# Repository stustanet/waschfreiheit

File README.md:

# Waschen in Freiheit !!!
## Was ist das?
Dieses Projekt soll verhindern, dass die armen Studenten unnötig lange mit der Suche nach einer freien Waschmaschine verbringen. Dazu soll der Status aller Maschinen erfasst werden um diese dann online abfragbar zu machen. Will man dann Waschen kann man direkt zu einer freien Maschine laufen und muss nicht erst in jedem Waschraum vorbeischauen, nur um festzustellen, dass dieser schon belegt ist.

## Aufbau
Der aktuelle Plan sieh in etwa so aus:

```
                                     +---+
+---Raum------------------------+    |   |
|                               |    | F |
|  WM <- Sensor  \              |    | U |
|                 => Knoten <~~~|~~~>| N |
|  WM <- Sensor  /              |    | K |
|                               |    |   |
+-------------------------------+    |   |
                                     |   |     +--------+    +-----------+
                                     |   |<~~~>| Bridge |--->| Webserver |
+---Raum------------------------+    |   |     +--------+    +-----------+
|                               |    |   |
|  WM <- Sensor  \              |    |   |
|                 => Knoten <~~~|~~~>|   |
|  WM <- Sensor  /              |    |   |
|                               |    |   |
+-------------------------------+    |   |
                                     |   |
                                     |   |
+---Raum------------------------+    |   |
|                               |    |   |
|  WM <- Sensor ===> Knoten <~~~|~~~>|   |
|                               |    |   |
+-------------------------------+    |   |
                                     +---+
    
```

### Sensoren
Ein Sensor misst den Stromverbrauch einer Maschine. Dies geschieht über einen Hallsensor am Stromkabel.

### Knoten
Ein Knoten besteht aus einem Mikroprozessor (STM32F103C8T6 (V1) oder STM32F401RBT6(V2), Kleiner 32bit ARM) und einem 433Mhz Funkchip (Sx1276, LoRa Modulation).
An einen Knoten sind ein oder mehrere Sensoren angeschlossen. Die Sensordaten werden dann ausgewertet und bei einer Statusänderung wird ein Signal über die Funkschnittstelle gesendet.
Außerdem ist es die Aufgabe eines Knotens Nachrichten anderer Knoten weiterzuleiten, diese bilden quasi ein Mesh Netzwerk.

### Bridge
Es gibt im ganzen System genau eine Bridge (Gateway, Master Node), diese besteht aus einem Funkteil und einem Raspi. Die Aufgabe der Bridge ist es die Statusänderungen vom Mesh Netzwerk zu empfangen und diese dann per IP an einen Webserver weiterzuleiten, der diese dann anzeigt. Zusätzlich verwaltet die Bridge das Netzwerk und die Sensorparameter.

### Webserver
Der Webserver bekommt die Daten von der Bridge und zeigt den aktuellen Status an.

## Statuserkennung
Die Statuserkennung basiert auf Messwerten, die ein am Stromkabel befestigter Hall-Sensor liefert.
Um aus diesen Werten schlussendlich zu erkennen ob eine Maschine in Benutzung ist, durchläuft das Signal eine Reihe von Filtern.

### Analoger Teil
#### Wechselspannungs-Verstärker
Zuerst wird das Signal vom Hall-Sensor verstärkt. Der Verstärker hat für DC einen Verstärkungsfaktor von 1, es werden also nur Änderungen verstärkt.
#### Tiefpass
Bevor das Signal vom ADC digitalisiert wird, wird es mit einem RC-Filter geglättet. Dieser Tiefpass darf nicht zu träge sein, eine höhere Trägheit die Amplitude verringert.

### Digitaler Filter, Stufe 1 (Input)
Die erste Stufe bekommt die Messwerte des ADCs, sie wird für jede Messung einmal aufgerufen.
#### Absolutwertbestimmung
Da das Signal eine Wechselspannung mit dem Mittelpunkt von ca. der halben Betriebsspannung ist, muss zuerst der Absolutwert (Abweichung vom Mittelwert) bestimmt werden.
Dazu wird ein Mittelwert bestimmt, der für jeden Messwert, der drüber liegt um einen kleinen Wert erhöht wird (bzw. verringert wird, wenn der Messwert niedrieger ist).
Die Differenz zwischen dem Mittelwert und dem aktuellen Messwert ist der Absolutwert.
#### Digitaler Tiefpass
Der Absolutwert wird über einen Digitalen Tiefpass geglättet. Hier ist eine wesentlich stärkere Glättung möglich als vor dem Absolutwertfilter, da keine Amplitude verloren geht.

### Digitaler Filter, Stufe 2 (Frames)
In bestimmten Abständen (Frames) wird der aktuelle Tiefpasswert der Stufe 1 an die Stufe 2 weitergegeben. Der Abstand ist die "Framesize"
Die Stufe 2 wird einmal pro Frame aktualisiert. Die letzten "Window Size" Frame-Werte werden gespeichert, aus diesen wird der aktuelle Wert des Filters berechnet.
#### Blockfilter (Consec reject filter)
Alle Werte die nicht größer als ein Grenzwert ("Reject Threshold") sind und nicht mind. "Reject Consec" Werte davor auch über dem Grenzwert liegen werden bei der Berechnung des aktuellen Wertes ignoriert.

Beispiel:
Angenommen der Threshold wäre 5 und der "Consec count" wäre 3, dann würden nur die markierten Werte verwendet werden.

    3 9 8 2 7 8 9 6 3 4 9 2 1 6 7 8 9 9 9 3 4 7 8 2
            ^ ^ ^ ^           ^ ^ ^ ^ ^ ^

#### Durchschnittswert
Der aktuelle Filterwert ist der Durchschnitt aller Werte im aktuellen Fenster. Werte die vom Blockfilter ignoriert werden gehen mit 0 in den Durchschnitt ein.
#### Interner Status
Abhängig vom aktuellen Filterwert und dem aktuellen internen Status wird anhand von festgelegten Grenzwerten bestimmt, ob ein Zustandsübergang stattfindet.
Bei einem Zustandsübergang wird ggf. die "Window Size" angepasst. Für jeden internen Zustand ist festgelegt, ob die Maschine in diesem Zustand belegt oder frei ist.
Nur Änderungen des Belegtzustandes werden über das Netzwerk gesendet.

## Ich will das complien!
* Ggf. ARM Toolchain installieren.
* Dieses Repo klonen.
* git submodule init
* git submodule update
* "make all" im Ordner firmware baut Master (V1 / V2), Sensor (V1 / V2) und den Bootloader (nur V2)

## Flashen
Es gibt eine Reihe verschiedener Möglichkeiten die Firmware zu flashen.
Manche sind nur auf V1 oder V2 verfügbar.

### ST-LINK
Die bequemste Möglichkeit diese Controller zu flashen ist ein ST-LINK. Dies ist ein spezieller Programmer / Debugger für ST Controller. Um einen ST-LINK zu verwenden muss OpenOCD installiert sein.

#### Benötigte Anschlüsse
Um mit einen ST-LINK zu flashen müssen folgende 3 / 4 Leitungen mit dem Board verbunden werden:
* GND
* SWIO
* SWCLK
* Ggf. 3.3V

Flashen geht dann einfach mit
```
Sensor V1
make flash_sv1

Sensor V2
make USE_BOOTLOADER=FALSE flash_sv2

Master V1
make flash_mv1

Master V2
make flash_mv2

Bootloader V2
make flash_blv2
```

### Serieller Bootloader
Das Board muss über ein Serielles Kabel mit dem PC verbunden werden.

Der flasher Tool stm32loader.py befindet sich als submodule in firmware/utils.

Das Kabel wird wie folgt angesteckt:
* RX von Kabel an TX vom Board
* TX von Kabel an RX vom Board
* GND an GND
* Ggf. die 5V von USB and die 5V(!) vom Board anschließen

Um das Board in den Bootloader Modus zu bringen:
#### V1
* Den BOOT0 Jumper auf 1 setzen
* Reset kurz drücken
* Nach dem Flashen den BOOT0 Jumper auf 0 zurüksetzen

#### V2
* Boot drücken und halten
* Reset kurz drücken
* Boot wieder loslassen

Zum flashen dann
```
Binary erstellen mit
arm-none-eabi-objcopy -I ihex -O binary <ELF> /tmp/image.bin

flashen mit
./stm32loader.py -p /dev/ttyUSB0 -evw /tmp/image.bin
```

### USB DFU Bootloader (Nur V2)

Dazu muss zuerst das tool dfu-util gebaut werden.
Dieses ist als submodule in firmware/utils eingebunden.

```
cd firmware/utils
./autogen.sh
./configure
make
```

Das Board wird dann über ein Micro-USB Kabel mit dem PC verbunden.
Um das Board in den Bootloader Modus zu bringen:
* Boot drücken und halten
* Reset kurz drücken
* Boot wieder loslassen

Dann sollte es sich am PC als DFU Gerät anmelden.
Zum flashen dann
```
Binary erstellen mit
arm-none-eabi-objcopy -I ihex -O binary <ELF> /tmp/image.bin

flashen mit
sudo ./dfu-util -a 0 -s 0x08000000:leave -D /tmp/image.bin
```

### USB Host Bootloader (Nur Sensor V2)
Der USB Host Bootloader ist ein eigener Bootloader für diese Boards, der es erlaubt ein Firmware image auf einen USB-Stick zu laden und dann ohne einen PC ein Update einzuspielen.
Um diesen zu verwenden, muss das Firmware Image für den Bootloader gebaut werden (ohne USE_BOOTLOADER=FALSE) und der Bootloader muss geflasht sein (das geht mit einer der anderen Methoden).

Auf einen FAT32 formatierten USB Stick müssen sich folgende Dateien befinden:
* FIRMWARE.BIN  Neue Firmware im Binärformat
* CHECKSUM.CRC  CRC32 Prüfsumme der Firmware

Diese beiden Dateien können bequem mit make_boot_files.sh in firmware/utils aus einer ELF erstellt werden.

Dann den Stick einfach an das Board anstecken und resetten. Die Eingangs-LEDs sollten während des Updates der Reihe nach in den Farben Grün, Violett, Rot und Gelb aufleuchten.
Nach dem Flashen wird das Programm normal gestartet.

Der USB Stick wird *nicht* erkannt, wenn dass Board über den Micro-USB Anschluss mit Strom versorgt wird.

### Flasher command (Nur V1)
Die V1 Boards haben einen integrierten Flash-Befehl mit dem die Firmware aus dem laufenden Betrieb heraus geupdated werden kann.
Da dazu nur die Serielle Schnittstelle benötigt wird und nicht extra ein Boot-Modus aktiviert werden muss ist dieser Modus praktisch um die alten Nodes zu flashen, da diese schlecht zu Öffnen sind.
Der Nachteil ist, dass sich der Flasher selbst überschreibt, d.h. sollte etwas schiefgehen, ist der Knoten über diesen Weg nicht erneut flashbar.

Das Tool zum flashen ist firmware/utils/flasher_v1.py

Zum flashen
```
Binary erstellen mit
arm-none-eabi-objcopy -I ihex -O binary <ELF> /tmp/image.bin

flashen mit
./flasher_v1.py /dev/ttyUSB0 /tmp/image.bin
```

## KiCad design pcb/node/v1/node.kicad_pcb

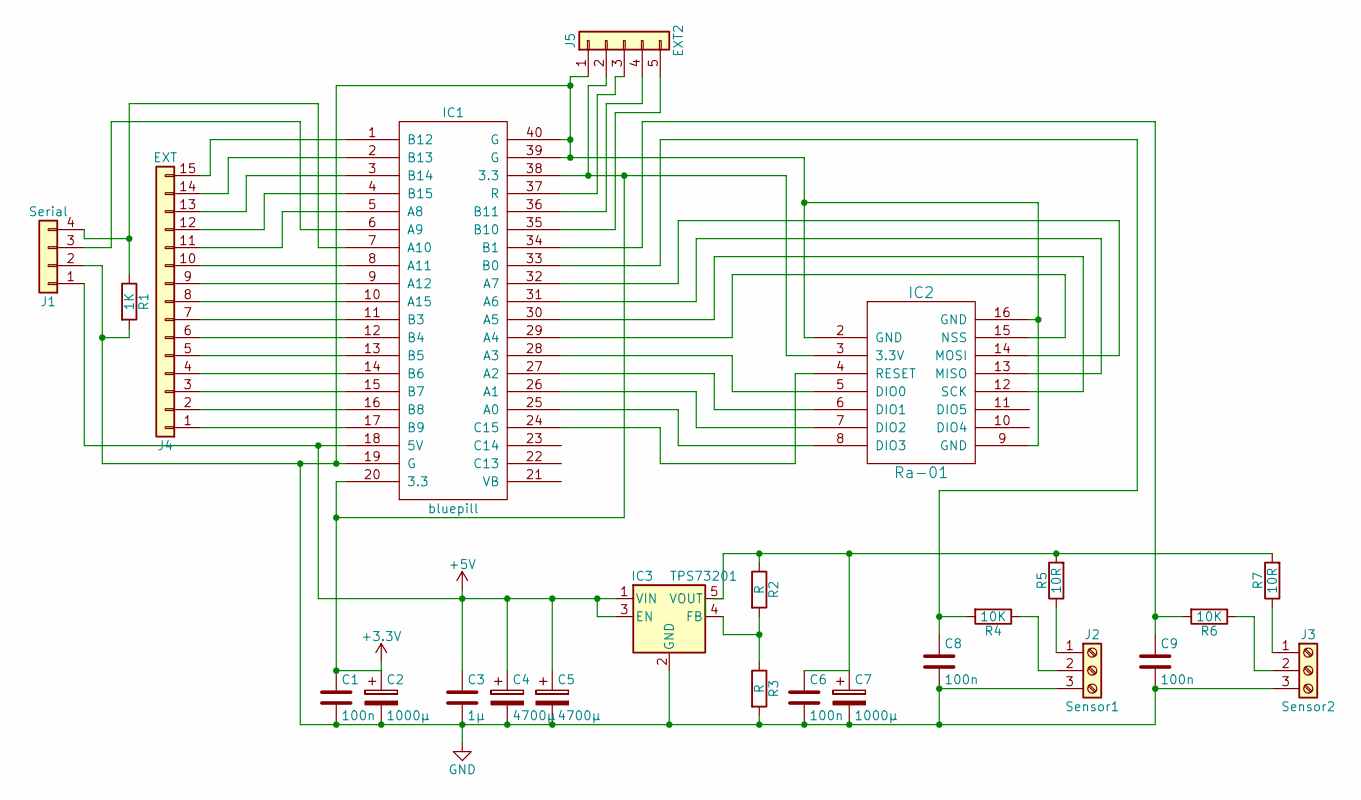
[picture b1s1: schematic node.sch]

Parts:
C1, C6, C8, C9: 100n; C_Disc_D5.0mm_W2.5mm_P2.50mm
C2, C7: 1000µ; CP_Radial_D10.0mm_P5.00mm
C3: 1µ; C_Disc_D7.5mm_W5.0mm_P5.00mm
C4, C5: 4700µ; CP_Radial_D12.5mm_P5.00mm
IC1: bluepill; DIP-40_W15.24mm
IC2: Ra-01
IC3: TPS73201; SOT-23-5
J1: Serial; Pin_Header_Straight_1x04_Pitch2.54mm
J2: Sensor1; TerminalBlock_Philmore_TB133_03x5mm_Straight
J3: Sensor2; TerminalBlock_Philmore_TB133_03x5mm_Straight
J4: EXT; Pin_Header_Straight_1x15_Pitch2.54mm
J5: EXT2; Pin_Header_Straight_1x05_Pitch2.54mm
R1: 1K; R_Axial_DIN0309_L9.0mm_D3.2mm_P12.70mm_Horizontal
R2, R3: R; R_0805
R4, R6: 10K; R_Axial_DIN0309_L9.0mm_D3.2mm_P12.70mm_Horizontal
R5, R7: 10R; R_Axial_DIN0309_L9.0mm_D3.2mm_P12.70mm_Horizontal

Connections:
+3V3: C1.1, C2.1, IC1.20 (3.3), IC1.38 (3.3), IC2.3 (3.3V), J5.2
+5V: C3.1, C4.1, C5.1, IC1.18 (5V), IC3.1 (VIN), IC3.3 (EN), J1.1
GND: C1.2, C2.2, C3.2, C4.2, C5.2, C6.2, C7.2, C8.2, C9.2, IC1.19 (G), IC1.39 (G), IC1.40 (G), IC2.2 (GND), IC2.9 (GND), IC2.16 (GND), IC3.2 (GND), J1.2, J2.3, J3.3, J5.1, R1.2, R3.2
unnamed: C6.1, C7.1, IC3.5 (VOUT), R2.1, R5.2, R7.2
unnamed: C8.1, IC1.33 (B0), R4.2
unnamed: C9.1, IC1.34 (B1), R6.2
unnamed: IC1.1 (B12), J4.15
unnamed: IC1.2 (B13), J4.14
unnamed: IC1.3 (B14), J4.13
unnamed: IC1.4 (B15), J4.12
unnamed: IC1.5 (A8), J4.11
unnamed: IC1.6 (A9), J1.3
unnamed: IC1.7 (A10), J1.4, R1.1
unnamed: IC1.8 (A11), J4.10
unnamed: IC1.9 (A12), J4.9
unnamed: IC1.10 (A15), J4.8
unnamed: IC1.11 (B3), J4.7
unnamed: IC1.12 (B4), J4.6
unnamed: IC1.13 (B5), J4.5
unnamed: IC1.14 (B6), J4.4
unnamed: IC1.15 (B7), J4.3
unnamed: IC1.16 (B8), J4.2
unnamed: IC1.17 (B9), J4.1
unnamed: IC1.24 (C15), IC2.4 (RESET)
unnamed: IC1.25 (A0), IC2.8 (DIO3)
unnamed: IC1.26 (A1), IC2.7 (DIO2)
unnamed: IC1.27 (A2), IC2.6 (DIO1)
unnamed: IC1.28 (A3), IC2.5 (DIO0)
unnamed: IC1.29 (A4), IC2.15 (NSS)
unnamed: IC1.30 (A5), IC2.12 (SCK)
unnamed: IC1.31 (A6), IC2.13 (MISO)
unnamed: IC1.32 (A7), IC2.14 (MOSI)
unnamed: IC1.35 (B10), J5.5
unnamed: IC1.36 (B11), J5.4
unnamed: IC1.37 (R), J5.3
unnamed: IC3.4 (FB), R2.2, R3.1
unnamed: J2.1, R5.1
unnamed: J2.2, R4.1
unnamed: J3.1, R7.1
unnamed: J3.2, R6.1

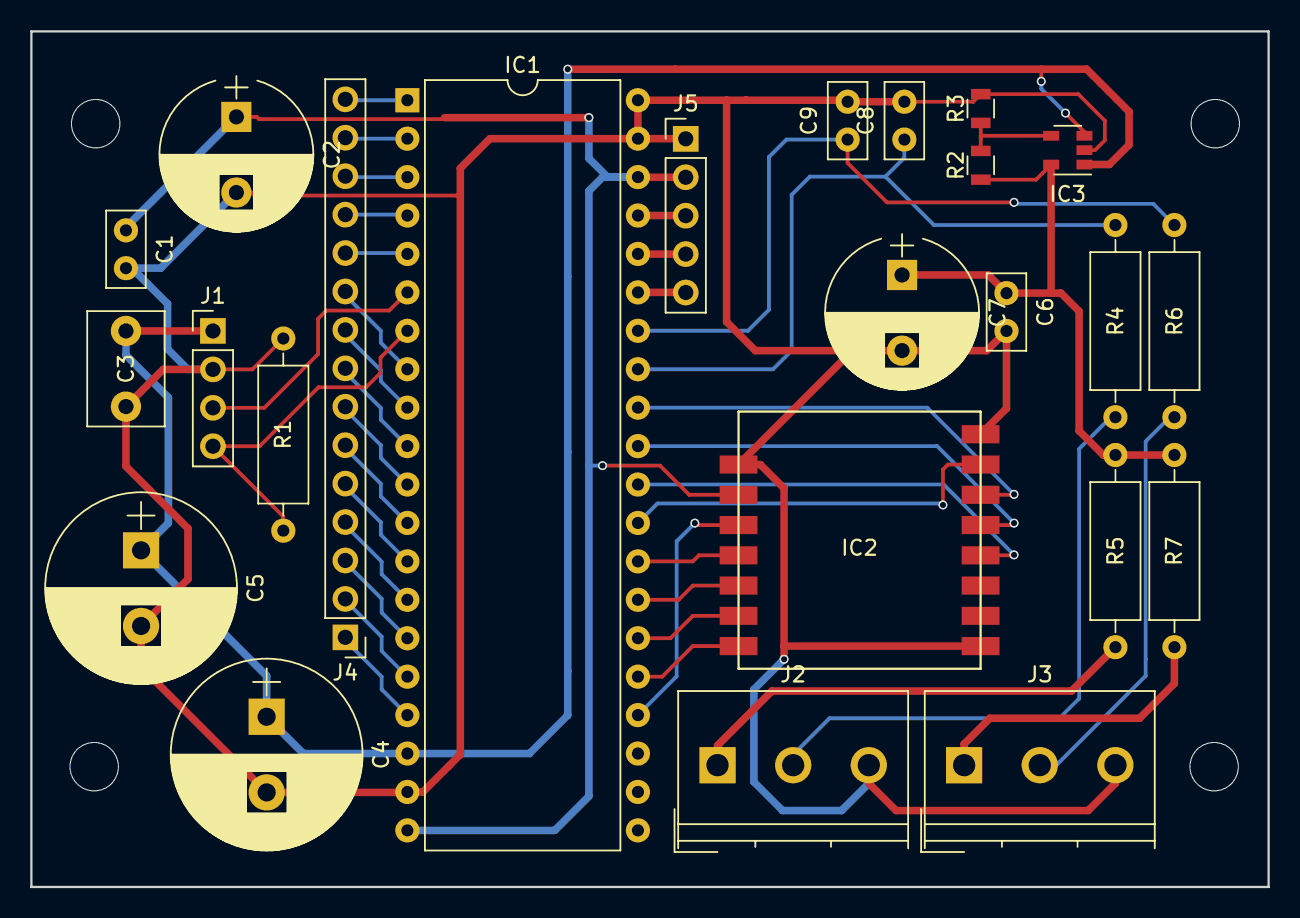
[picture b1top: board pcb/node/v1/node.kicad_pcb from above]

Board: 2 copper layers, 81.8 x 56.5 mm, 24 parts (0 on the bottom side), 40 nets.

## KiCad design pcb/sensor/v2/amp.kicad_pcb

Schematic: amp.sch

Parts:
C1: 1000µ; R_1206
C2: 22µ; R_0805
C3: 100n; R_0805
IC1: 49E; TO-92_Inline_Narrow_Oval
IC2: LM358; VSSOP-8_3.0x3.0mm_Pitch0.65mm
J1: TO MCU; Pin_Header_Straight_1x03_Pitch2.54mm
R1: 1K; R_0805
R2: 10K; R_0805
R3: 4K7; R_0805
R4: 3R3; R_0805

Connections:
+5V: C1.1, C3.1, IC1.1, IC2.8 (V+), R4.2
GND: C1.2, C2.2, C3.2, IC1.2, IC2.4 (V-), J1.3
unnamed: C2.1, R1.2
unnamed: IC1.3, IC2.5 (+)
unnamed: IC2.6 (-), R1.1, R2.2
unnamed: IC2.7, R2.1, R3.2
unnamed: J1.1, R3.1
unnamed: J1.2, R4.1

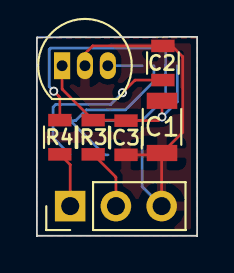
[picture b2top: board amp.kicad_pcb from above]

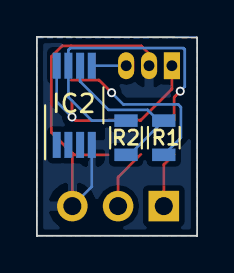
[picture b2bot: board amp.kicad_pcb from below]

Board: 2 copper layers, 8.9 x 11.1 mm, 10 parts (3 on the bottom side), 8 nets.

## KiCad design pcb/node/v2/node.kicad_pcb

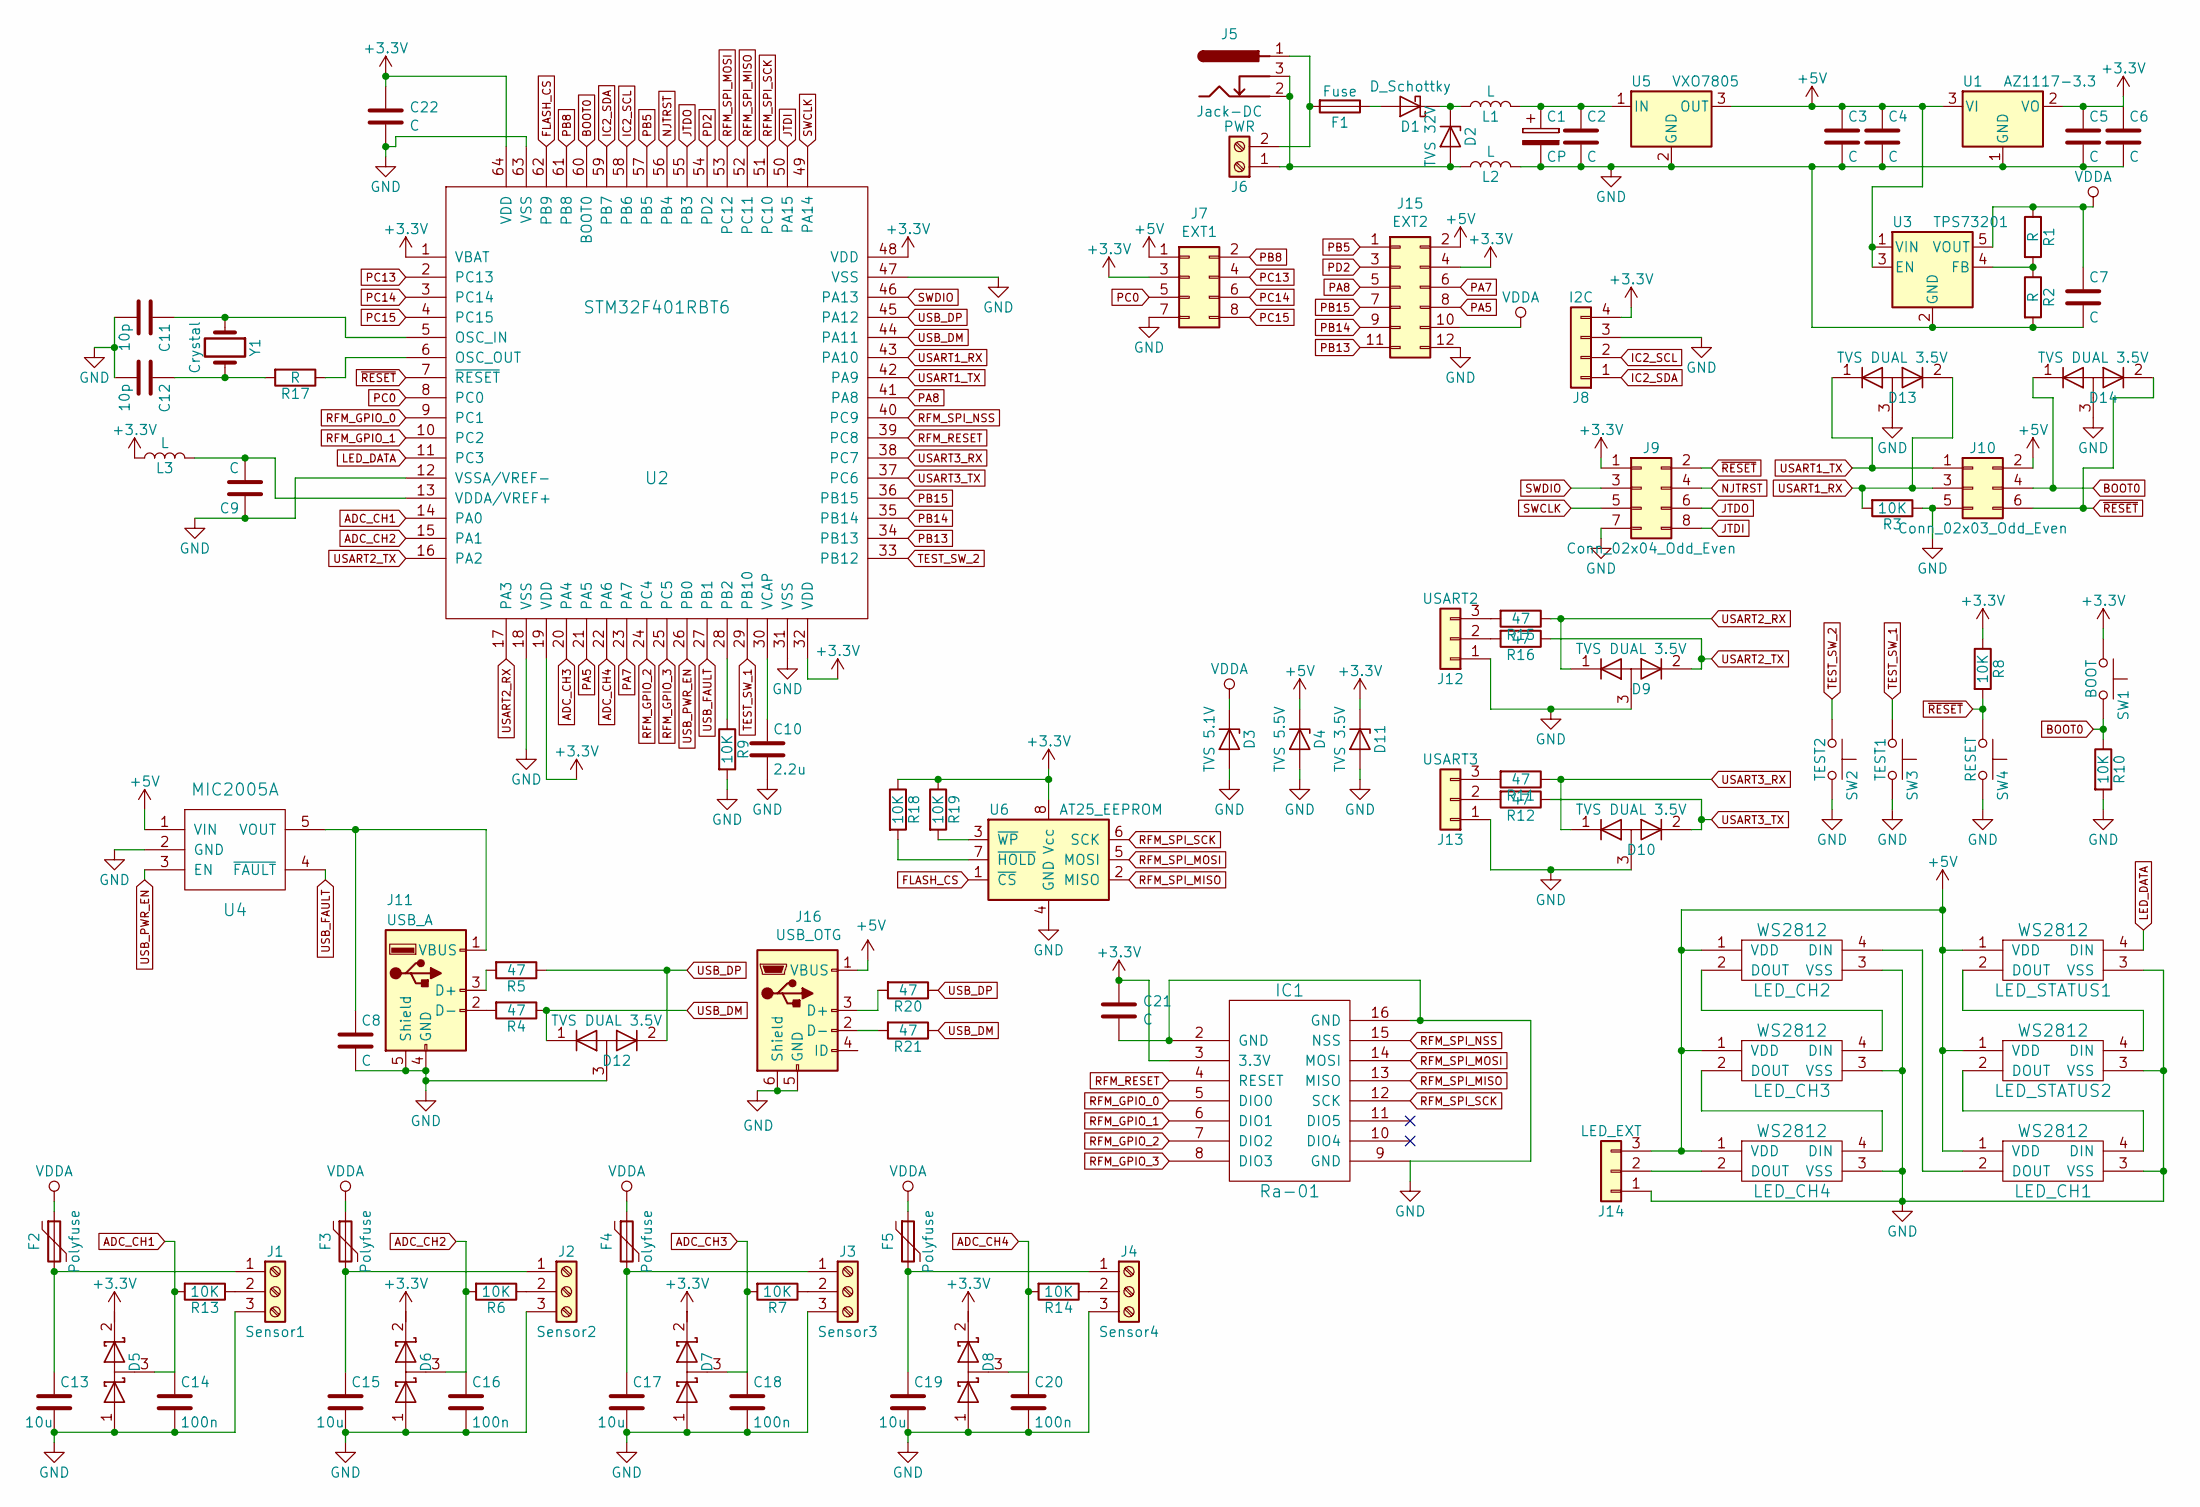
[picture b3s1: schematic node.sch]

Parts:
C1: CP; CP_Radial_D10.0mm_P5.00mm
C2, C3, C5, C21, C22: C; C_0805
C4, C6, C7, C8, C9: C; C_1206
C10: 2.2u; C_0805
C11, C12: 10p; C_0805
C13, C15, C17, C19: 10u; C_0805
C14, C16, C18, C20: 100n; C_0805
D1: D_Schottky; D_SOD-323
D2: TVS 32V; D_2010
D3: TVS 5.1V; D_SOD-323
D4: TVS 5.5V; D_SOD-323
D5, D6, D7, D8: D_Schottky_x2_Serial_AKC; SOT-23
D9, D10, D12, D13, D14: TVS DUAL 3.5V; SOT-23
D11: TVS 3.5V; D_SOD-323
F1: Fuse; Fuse_SMD
F2, F3, F4, F5: Polyfuse; SMD-1210_Pol
IC1: Ra-01
J1: Sensor1; Ampernol_3_3.5_hor
J2: Sensor2; Ampernol_3_3.5_hor
J3: Sensor3; Ampernol_3_3.5_hor
J4: Sensor4; Ampernol_3_3.5_hor
J5: Jack-DC; BARREL_JACK
J6: PWR; TerminalBlock_4UCON_19963_02x3.5mm_Straight
J7: EXT1; Pin_Header_Straight_2x04_Pitch2.54mm
J8: I2C; Pin_Header_Straight_1x04_Pitch2.54mm
J9: Conn_02x04_Odd_Even; Pin_Header_Straight_2x04_Pitch2.54mm
J10: Conn_02x03_Odd_Even; Pin_Header_Straight_2x03_Pitch2.54mm
J11: USB_A; USB_F_VERT
J12: USART2; Pin_Header_Straight_1x03_Pitch2.54mm
J13: USART3; Pin_Header_Straight_1x03_Pitch2.54mm
J14: LED_EXT; Pin_Header_Straight_1x03_Pitch2.54mm
J15: EXT2; Pin_Header_Straight_2x06_Pitch2.54mm
J16: USB_OTG; USB_Micro-B_10103594-0001LF
L1, L2, L3: L; Choke_SMD_1206_Standard
LED_CH1, LED_CH2, LED_CH3, LED_CH4: WS2812; LED_WS2812B-PLCC4
LED_STATUS1, LED_STATUS2: WS2812; LED_WS2812B-PLCC4
R1, R2, R17: R; R_0805
R3, R6, R7, R8, R9, R10, R13, R14, R18, R19: 10K; R_0805
R4, R5, R11, R12, R15, R16, R20, R21: 47; R_0805
SW1: BOOT; SW_SPST_PTS645
SW2: TEST2; SW_SPST_PTS645
SW3: TEST1; SW_SPST_PTS645
SW4: RESET; SW_SPST_PTS645
U1: AZ1117-3.3; SOT-223-3Lead_TabPin2
U2: STM32F401RBT6; LQFP-64_10x10mm_Pitch0.5mm
U3: TPS73201; SOT-23-5
U4: MIC2005A; SOT-23-5
U5: VXO7805; TO-220_Vertical
U6: AT25_EEPROM; SOIC-8_3.9x4.9mm_Pitch1.27mm
Y1: Crystal; Crystal_SMD_HC49-SD

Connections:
+3V3: C5.1, C6.1, C21.1, C22.1, D5.2 (K), D6.2 (K), D7.2 (K), D8.2 (K), D11.1 (K), IC1.3 (3.3V), J7.3, J8.4, J9.1, J15.4, L3.1, R8.1, R18.1, R19.1, SW1.1, U1.2 (VO), U2.1 (VBAT), U2.19 (VDD), U2.32 (VDD), U2.48 (VDD), U2.64 (VDD), U6.8 (Vcc)
+5V: C3.1, C4.1, D4.1 (K), J7.1, J10.2, J14.3, J15.2, J16.1 (VBUS), LED_CH1.1 (VDD), LED_CH2.1 (VDD), LED_CH3.1 (VDD), LED_CH4.1 (VDD), LED_STATUS1.1 (VDD), LED_STATUS2.1 (VDD), U1.3 (VI), U3.1 (VIN), U3.3 (EN), U4.1 (VIN), U5.3 (OUT)
ADC_CH1: C14.1, D5.3 (common), R13.2, U2.14 (PA0)
ADC_CH2: C16.1, D6.3 (common), R6.2, U2.15 (PA1)
ADC_CH3: C18.1, D7.3 (common), R7.2, U2.20 (PA4)
ADC_CH4: C20.1, D8.3 (common), R14.2, U2.22 (PA6)
BOOT0: D14.1 (K), J10.4, R10.1, SW1.2, U2.60 (BOOT0)
FLASH_CS: U2.62 (PB9), U6.1 (~CS)
GND: C1.2, C2.2, C3.2, C4.2, C5.2, C6.2, C7.2, C8.2, C9.1, C10.2, C11.2, C12.2, C13.2, C14.2, C15.2, C16.2, C17.2, C18.2, C19.2, C20.2, C21.2, C22.2, D3.2 (A), D4.2 (A), D5.1 (A), D6.1 (A), D7.1 (A), D8.1 (A), D9.3 (A), D10.3 (A), D11.2 (A), D12.3 (A), D13.3 (A), D14.3 (A), IC1.2 (GND), IC1.9 (GND), IC1.16 (GND), J1.3, J2.3, J3.3, J4.3, J7.7, J8.3, J9.7, J10.5, J11.4 (GND), J11.5 (Shield), J12.1, J13.1, J14.1, J15.12, J16.5 (GND), J16.6 (Shield), L2.2, LED_CH1.3 (VSS), LED_CH2.3 (VSS), LED_CH3.3 (VSS), LED_CH4.3 (VSS), LED_STATUS1.3 (VSS), LED_STATUS2.3 (VSS), R2.2, R3.1, R9.2, R10.2, SW2.2, SW3.2, SW4.2, U1.1 (GND), U2.12 (VSSA/VREF-), U2.18 (VSS), U2.31 (VSS), U2.47 (VSS), U2.63 (VSS), U3.2 (GND), U4.2 (GND), U5.2 (GND), U6.4 (GND)
IC2_SCL: J8.2, U2.58 (PB6)
IC2_SDA: J8.1, U2.59 (PB7)
JTDI: J9.8, U2.50 (PA15)
JTDO: J9.6, U2.55 (PB3)
LED_DATA: LED_STATUS1.4 (DIN), U2.11 (PC3)
NJTRST: J9.4, U2.56 (PB4)
unnamed: C1.1, C2.1, L1.2, U5.1 (IN)
unnamed: C8.1, J11.1 (VBUS), U4.5 (VOUT)
unnamed: C9.2, L3.2, U2.13 (VDDA/VREF+)
unnamed: C10.1, U2.30 (VCAP)
unnamed: C11.1, U2.5 (OSC_IN), Y1.1
unnamed: C12.1, R17.2, Y1.2
unnamed: C13.1, F2.2, J1.1
unnamed: C15.1, F3.2, J2.1
unnamed: C17.1, F4.2, J3.1
unnamed: C19.1, F5.2, J4.1
unnamed: D1.1 (K), D2.1 (K), L1.1
unnamed: D1.2 (A), F1.1
unnamed: D2.2 (A), J5.2, J5.3, J6.1, L2.1
unnamed: F1.2, J5.1, J6.2
unnamed: J1.2, R13.1
unnamed: J2.2, R6.1
unnamed: J3.2, R7.1
unnamed: J4.2, R14.1
unnamed: J11.2 (D-), R4.2
unnamed: J11.3 (D+), R5.2
unnamed: J12.2, R16.2
unnamed: J12.3, R15.2
unnamed: J13.2, R12.2
unnamed: J13.3, R11.2
unnamed: J14.2, LED_CH4.2 (DOUT)
unnamed: J16.2 (D-), R21.2
unnamed: J16.3 (D+), R20.2
unnamed: LED_CH1.2 (DOUT), LED_CH2.4 (DIN)
unnamed: LED_CH1.4 (DIN), LED_STATUS2.2 (DOUT)
unnamed: LED_CH2.2 (DOUT), LED_CH3.4 (DIN)
unnamed: LED_CH3.2 (DOUT), LED_CH4.4 (DIN)
unnamed: LED_STATUS1.2 (DOUT), LED_STATUS2.4 (DIN)
unnamed: R1.2, R2.1, U3.4 (FB)
unnamed: R9.1, U2.28 (PB2)
unnamed: R17.1, U2.6 (OSC_OUT)
unnamed: R18.2, U6.7 (~HOLD)
unnamed: R19.2, U6.3 (~WP)
PA5: J15.8, U2.21 (PA5)
PA7: J15.6, U2.23 (PA7)
PA8: J15.5, U2.41 (PA8)
PB5: J15.1, U2.57 (PB5)
PB8: J7.2, U2.61 (PB8)
PB13: J15.11, U2.34 (PB13)
PB14: J15.9, U2.35 (PB14)
PB15: J15.7, U2.36 (PB15)
PC0: J7.5, U2.8 (PC0)
PC13: J7.4, U2.2 (PC13)
PC14: J7.6, U2.3 (PC14)
PC15: J7.8, U2.4 (PC15)
PD2: J15.3, U2.54 (PD2)
RFM_GPIO_0: IC1.5 (DIO0), U2.9 (PC1)
RFM_GPIO_1: IC1.6 (DIO1), U2.10 (PC2)
RFM_GPIO_2: IC1.7 (DIO2), U2.24 (PC4)
RFM_GPIO_3: IC1.8 (DIO3), U2.25 (PC5)
RFM_RESET: IC1.4 (RESET), U2.39 (PC8)
RFM_SPI_MISO: IC1.13 (MISO), U2.52 (PC11), U6.2 (MISO)
RFM_SPI_MOSI: IC1.14 (MOSI), U2.53 (PC12), U6.5 (MOSI)
RFM_SPI_NSS: IC1.15 (NSS), U2.40 (PC9)
RFM_SPI_SCK: IC1.12 (SCK), U2.51 (PC10), U6.6 (SCK)
SWCLK: J9.5, U2.49 (PA14)
SWDIO: J9.3, U2.46 (PA13)
TEST_SW_1: SW3.1, U2.29 (PB10)
TEST_SW_2: SW2.1, U2.33 (PB12)
USART1_RX: D13.2 (K), J10.3, R3.2, U2.43 (PA10)
USART1_TX: D13.1 (K), J10.1, U2.42 (PA9)
USART2_RX: D9.1 (K), R15.1, U2.17 (PA3)
USART2_TX: D9.2 (K), R16.1, U2.16 (PA2)
USART3_RX: D10.1 (K), R11.1, U2.38 (PC7)
USART3_TX: D10.2 (K), R12.1, U2.37 (PC6)
USB_DM: D12.1 (K), R4.1, R21.1, U2.44 (PA11)
USB_DP: D12.2 (K), R5.1, R20.1, U2.45 (PA12)
USB_FAULT: U2.27 (PB1), U4.4 (~FAULT)
USB_PWR_EN: U2.26 (PB0), U4.3 (EN)
VDDA: C7.1, D3.1 (K), F2.1, F3.1, F4.1, F5.1, J15.10, R1.1, U3.5 (VOUT)
~RESET: D14.2 (K), J9.2, J10.6, R8.2, SW4.1, U2.7 (~RESET)

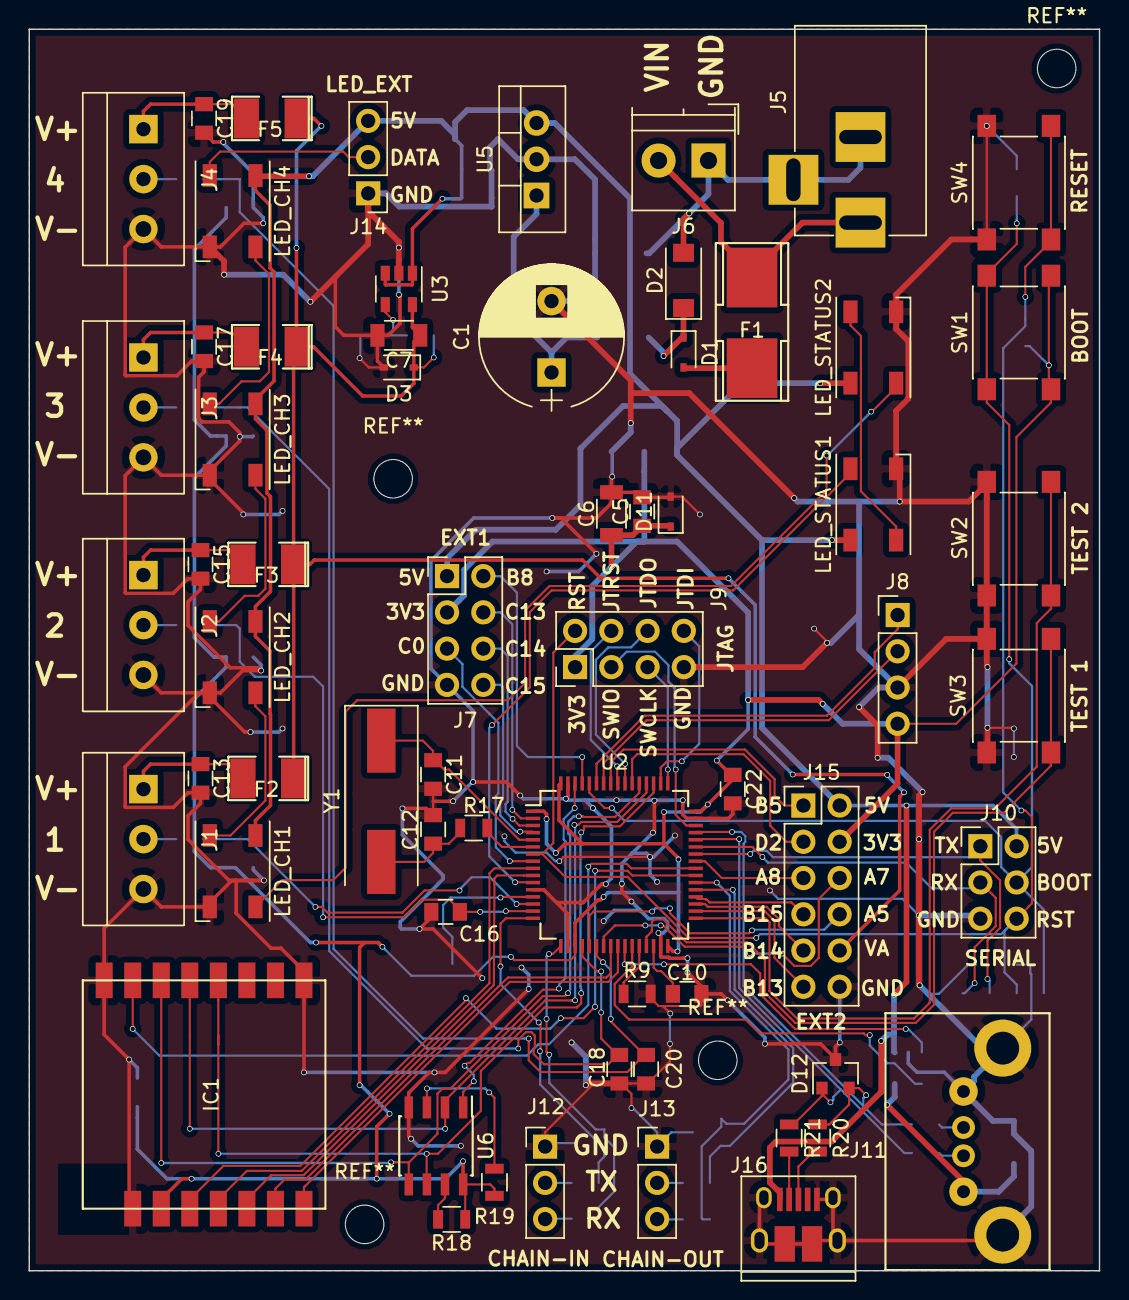
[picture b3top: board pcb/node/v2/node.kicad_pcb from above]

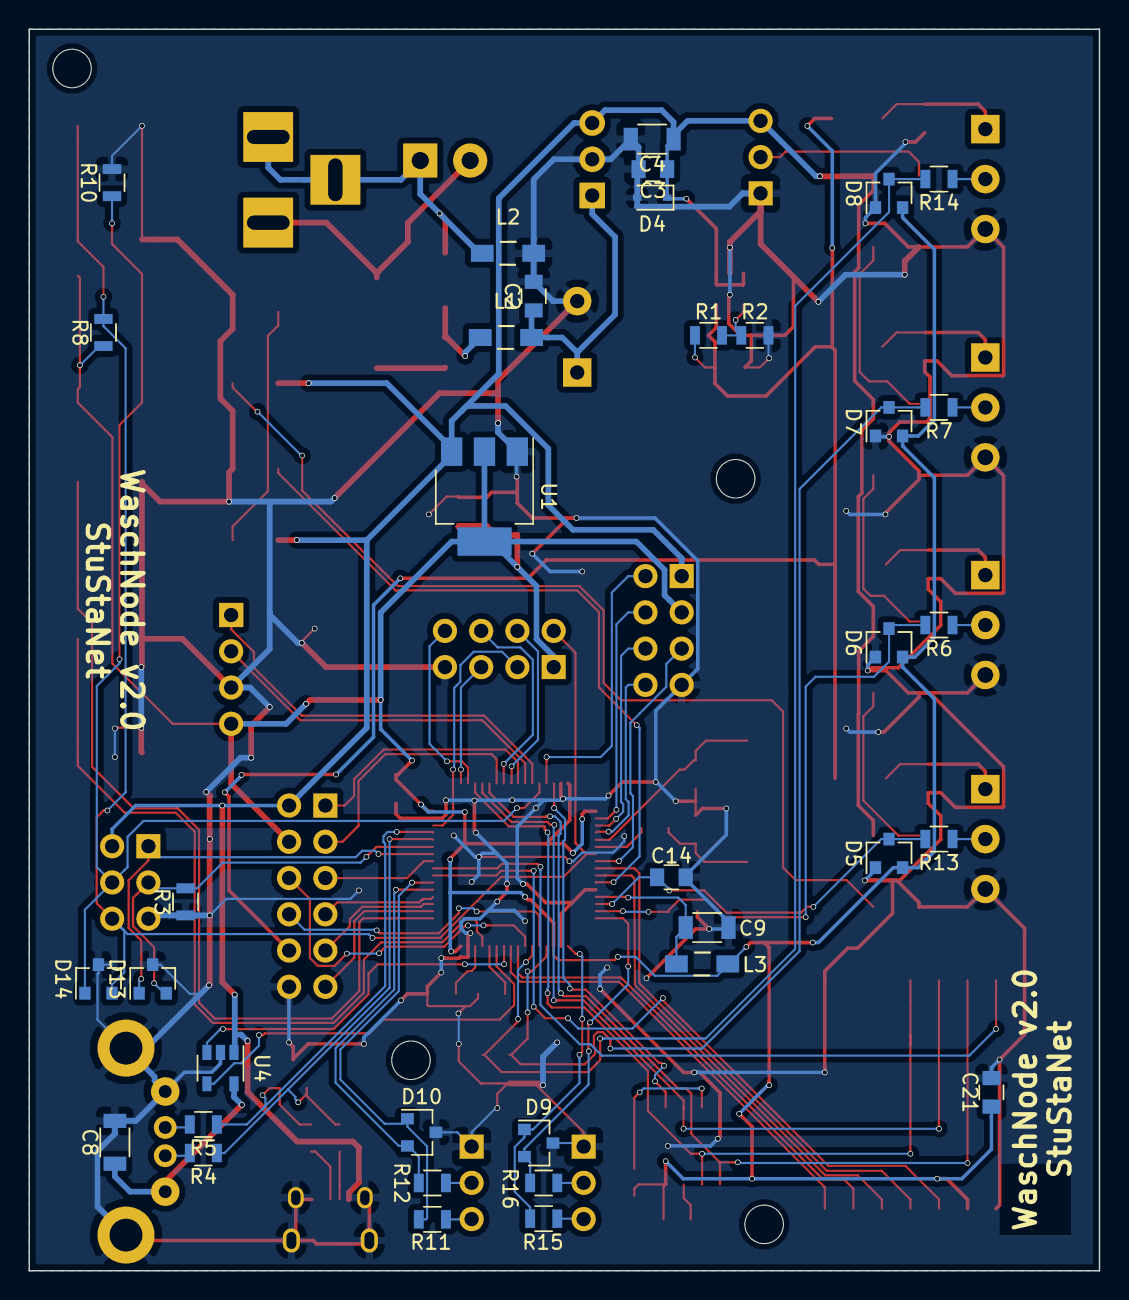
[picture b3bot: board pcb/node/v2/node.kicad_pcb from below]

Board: 2 copper layers, 75.0 x 87.0 mm, 99 parts (36 on the bottom side), 90 nets.

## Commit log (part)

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2018-03-08 WIP: Connection Management
2018-03-08 added machinemanager
2018-03-08 fixed error in debuginterface
2018-03-08 added systemd service file
2018-04-07 Changed master lora params
2018-04-07 Increased verbosity
2018-04-07 Activate forwaring if routes on a sensor are manually set
2018-04-07 Added flasher function
2018-04-07 firmware_upgrade command
2018-04-07 Added flasher util
2018-04-12 Fixed deadlock on CRC-error in network code
2018-04-24 Changed default spread factor
2018-04-24 Compile fix
2018-04-24 Added status code to connect result
2018-04-24 Improved flasher stability
2018-04-24 Added license headers and fixed some typos
2018-04-24 some old changes to the test script
2018-07-03 added install procedure
2018-07-03 wait for retry * hop * distance before seppuku
2018-07-03 Fixed build for new RIOT version
2018-07-03 Added rebuild_status_channel command to allow fast recovery after timeout
2018-07-03 added rebuild_status_channel for fast re-init
2018-07-03 Logging to logfile instead of stdout
2018-07-03 fixed at least one problem with heartbeats
2018-07-03 fixed typo in makefile
2018-07-03 changed systemd startup
2018-07-03 more systemd magic fun
2018-08-23 Connection Management for setup and recover
2018-08-23 Fixed random numbers being too short
2018-08-23 Changed adc thread prio to max to avoid xtimer bug
2018-08-23 use dma getchar
2018-08-23 Added timeout for sensor node
2018-08-23 Better initial mid value
2018-08-23 Added hardware watchdog
2018-08-23 Fixed condition
2018-08-23 Improved output of color command
2018-08-23 Added a "some" because some changes have immediate effect
2018-08-23 RF frequency and tx power are now configureable for the sensor node
2018-08-23 Missing }
2018-08-23 Removed evil whitespaces
2018-08-23 Fixed tx power settingC
2018-08-23 Fixed sensor status being wrong after reinit, missing file
2018-08-23 Also disable routing on route clear
2018-08-23 Reduced adc thread stack (has no auth)
2018-08-23 Fixed some comments
2018-08-23 Added colormap to config
2018-08-23 Set unititialized LEDs to 0
2018-08-23 Added some comments
2018-08-23 Added raw status debug cmmand
2018-08-23 Really fixed markdown
2018-08-23 added accessor functon for the current state
2018-08-23 Added util function to parse rgb values
2018-08-23 Added missing return statement on retransmissions
2018-08-23 Periodically re-set the LEDs
2018-08-23 Added color list
2018-08-23 config: done a hsh setup
2018-08-23 Added misc config
2018-08-23 Added DMA based getchar implementation
2018-08-23 Shorter auth footer
2018-08-23 Better comments
2018-08-23 Added more info about the configure_sensor command
2018-08-23 Very ugly (but working) collision avoidance
2018-08-23 Added missing defaults header
2018-08-23 Added status command
2018-08-23 Moved TOSTRING macro from debug_assert.h to utils.hC
2018-08-23 Improved timeout
2018-08-23 Even more comments
2018-08-23 Added mutex for shared access
2018-08-23 Revert "Very ugly (but working) collision avoidance"
    This reverts commit f126b57ae696448c748c69927571f4cd28e10fbb.
2018-08-23 rgb data parameter should be const
2018-08-23 Rearranged some code
2018-08-23 Improved debug output
2018-08-23 Use own board "wasch_v1" and fixed build for current RIOT version
2018-08-23 finetuning the retransmits
2018-08-23 Added message with id to sensor init
2018-08-23 Less confusion error if a channel is blocked by an outstanding ack
2018-08-23 added heartbeat feature
2018-08-23 Much better way to do the collision avoidance^^
2018-08-23 Fixed auth status not being reset when a new handshake is generated
2018-08-23 Fixed connect command
2018-08-23 Added mutex
2018-08-23 More fixes for new driver version
2018-08-23 Additional alignment check
2018-08-23 Status print is now ISR safe
2018-08-23 Added LED support
2018-08-23 Fixed sensor status being wrong after reinit
2018-08-23 New default color table
2018-08-23 Removed superflous delay in LED code
2018-08-23 Added adc thread watchdog
2018-08-23 do not crash on unfortunate combination of timeouts
2018-08-23 Fixed compile errors
2018-08-23 added readme
2018-08-23 added frames, status, led, shutdown to debuginterface
2018-08-23 re-enter listen mode when an unexpected event occures
2018-08-23 added uplink interface to update the website
2018-08-23 More LoRa config options
2018-08-23 Allow 0 as target for ping
2018-08-23 Added LED animation
2018-08-23 added a testing framework with socat
2018-08-23 re-send status after route_reset command
2018-08-23 small little bugfixes
2018-08-23 Added filter description to README
2018-08-23 now with extra exceptions
2018-08-23 Fixed typo
2018-08-23 Missing ws2801 driver
2018-08-23 Added "print_frames" debug command
2018-08-23 Added missing break
2018-08-23 Added raw command for node testing / setup
2018-08-23 Added missing init params for master
2018-08-23 added longely standing around parts
2018-09-19 rewrote pyinterface to be a state machine
2018-09-20 Setup network from config
2018-09-21 added global message uniqueness
2018-10-15 Perparation for porting to FreeRTOS and libopencm3: Copied files from mcu_riot/node
2018-10-15 Added FreeRTOS
2018-10-15 Added Makefiles and linker script
2018-10-15 Split project into master and sensor part
2018-10-15 Added gitignore
2018-10-15 Also split the headers into master and node
2018-10-15 Ignore all hiiden files
2018-10-16 Added tinyprintf
2018-10-16 Renamed makefiles to standard .mk extension
2018-10-16 Tinyprintf init
2018-10-17 Added CLI
2018-10-19 Added sx127x driver
2018-10-19 Sx127x driver test
2018-10-20 Don't abort tx if recv is called
2018-10-20 Ported meshnw
2018-10-20 Added cifra submodule for crypto
2018-10-20 Ported auth module
2018-10-20 Added build files for sensor node and ported led lib
2018-10-20 Added missing guard
2018-10-20 Ported sensor config
2018-10-20 Added define for board version 2
2018-10-20 Ported legacy node flasher and watchdog
2018-10-20 Ported sensor node and added ADC with DMA
2018-10-21 Ported master config and fixed build for legacy board
2018-10-21 Master and sensor now build for both board variants
2018-10-21 Added missing mutex init
2018-10-21 fixed result checking for meshnw_send
2018-10-21 I2S base led driver
2018-10-21 New status system
2018-10-21 Fixed led status
2018-10-21 forgot to commit
2018-10-21 Fixed master build
2018-10-21 Added status_change_indicator config command
2018-10-23 Added sx127x driver description
2018-10-23 Added modified version of libusbhost
2018-10-23 Added libusbhost to build
2018-10-23 Added usb_storage_helper wrapper for msc devices
2018-10-23 Added fatfs
2018-10-23 Build fatfs
2018-10-23 Build USBH FS driver and fixed usbh debug
2018-10-23 Ignore the FSTX state when checking the busy state
2018-10-23 Turn on the USB power
2018-10-23 Reduced prio and reset busy state on disconnect to avoid the poll thread blocking the CPU
2018-10-23 Currect LED status
2018-10-26 New makefiles
2018-10-26 Fixed "make clean"
2018-10-26 Fixed v1 sensor build
2018-10-26 Forgot to add this file
2018-10-28 Added frequency sensor
2018-10-28 Fixed wrong size of DMA transfer
2018-10-28 Fixed config command for legacy hardware
2018-10-28 Added flash_* make targets
2018-10-28 Added slight delay in sx127x init
2018-10-30 Fixed LEDs on legacy boards
2018-11-01 Moved i2s led impl to own dir
2018-11-01 Added MIT license files
2018-11-01 Added bootloader
2018-11-01 Set VTOR before jumping to app
2018-11-01 Added makefile and linker scripts for bootloader builds
2018-11-01 Moved flasher script
2018-11-01 Removed outdated comment
2018-11-01 New hello message
2018-11-01 Added option to build without bootloader
2018-11-01 Implemented test buttons
2018-11-01 This should be MIT, not GPL
2018-11-01 Added reboot command
2018-11-01 Use last page for master config
2018-11-01 Use reset instead of waiting for the wdt
2018-11-01 Added sanity check before enabling the sensor channel
2018-11-02 added manhattan sensor. running tests
2018-11-02 Fixed frequency sensor
2018-11-02 Fixed santity check also checking disabled channels
2018-11-02 Added an additional space to the help command
2018-11-02 Use "cfg_" instead of "configure_" and added freq chn config command
2018-11-02 Fixed modem getting stuck in FSTX mode
2018-11-02 Added sx127x test command to the master node
2018-11-06 Removed old riot based impl
2018-11-06 Added v2 PCBs and updated v1 versions to KiCad 5
2018-11-06 Removed old pcb files
2018-11-06 Moved description files to sensor dir and removed duplicates
2018-11-06 Added schematic as pdf
2018-11-06 Added stm32loader submodule
2018-11-06 Moved old scad files to v1 and add new sensor design
2018-11-07 Added missing part values
2018-11-07 Fixed markdown (again)
2018-11-24 Fixed erasing wrong config page in master_v1
2018-11-24 Added submodle init to README
2018-11-28 Fixed showing error message if the forward was OK
2018-12-04 Added ssi command
2018-12-04 Added current manhattan switch impl
2018-12-04 Fixed config
2018-12-04 Fixed device led state can be wrong if a status update happens before the LED update is confirmed
2018-12-05 More reliable init sequence for the modem
2018-12-05 Fixed high packet loss on long routes
2018-12-05 Added current mid value to debug print
2018-12-05 Do not attempt to connect to an unreachable node
2018-12-11 Hacky backport of the manhattan node impl to the old interface
2019-01-20 Removed now obsolete files
2019-01-20 Added lebt signal
2019-01-20 Added debug interface
2019-01-20 Fixed master restart not resetting the node status
2019-01-20 Added dumpstate debug command
2019-01-22 Added mute debug command
2019-01-23 Moved watchdog header becaues it will be used on the master as well
2019-01-24 Added host watchdog
2019-01-27 Removed old stuff
2019-01-27 Added gateway script
2019-01-27 Added fw upgrade script
2019-01-27 Added tcp server mode
2019-02-13 Connect to node
2019-02-13 Turn on status LED on V1 boards
2019-02-13 Added real config
2019-02-13 Corrected node IDs
2019-02-13 Fixed serial mode in master
2019-02-14 Fixed some problems of the debug interface
2019-02-14 Added extralog to uplink
2019-02-14 Better extralog
2019-02-14 Also print response type to log
2019-04-14 Remoived host watchdog again. The gateway will use a seperate controller as watchdog.
2019-04-14 Allow manual routes by adding the node numbers prefixed with a #
2019-04-14 Gateway must not force the reste line to 3.3v, otherwise the software reset of the mcu won't work
2019-04-14 Add watchdog prefail warning
2019-04-14 Added watchdog files
2019-04-14 Added copy of stm32loader to the gateway
2019-04-14 Added license header
2019-04-16 Config prefix
2019-04-16 Added logging
2019-04-17 Fixed install for the gateway
2019-04-18 Fixed controller hangup on debug interface disconnect
2019-04-18 New install files
2019-04-18 Fixed debug interface crash
2019-04-28 Fixed external LEDs not being updated for v2 nodes
2019-04-28 Better help for freq channel config command
2019-04-28 Increased network polling rate
2019-04-28 Status command now also prints if the channels are enabled
2019-04-28 New config with channel types
2019-04-28 added casing revision 2
2019-04-28 Added HSH18
2019-04-28 Reduced forwarding delay
2019-04-28 Added modem reset, when the modem drops out of LoRa mode
2019-04-28 restructured cad versions
2019-04-30 modified front plate to new casing height
2019-04-30 df wanted .5mm, df got .5mm. twice.
2019-05-01 Added profile for dryers
2019-05-01 Build bootloader with -Os
2019-05-01 Normal nodes have 5 status LEDs
2019-05-04 Added remote storage management
2019-05-04 Added storage_ctl command
2019-05-04 Also print state dump on empty command
2019-05-04 Show the route status in the state dump
2019-05-05 Added HSH18 to led map
2019-05-14 Removed unused import
2019-05-22 Added PEND signal to increase the robustness of the serial interface
2019-05-22 Removed annoying debug
2019-06-10 Fixed frame value logging
2020-04-17 Added node_alive signal
2020-04-17 Removed LED command as it would invalidate the internal status
2020-04-17 Added retry command to manually reset the reconnect timeouts
2020-04-20 Implicitly define the master route by the gateway
2020-05-02 Always print an error status when a command fails
